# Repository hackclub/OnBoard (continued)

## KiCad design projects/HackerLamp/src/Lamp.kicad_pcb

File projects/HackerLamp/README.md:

---
name: "Aarav Jhamb"
slack_handle: "@AaravJ"
github_handle: "@The-UnknownHacker"
tutorial: None
wokwi: # Link to the Wokwi project if you're submitting for Hacky Holidays
---

# Wifi Powered Lamp

<!-- Describe your board in 2-3 sentences. What are you making? What will it do? -->

It is a wifi powered lamp powered by an ESP32 C3 Xiao and Uses 100 neopixels as power
<!-- How much is it going to cost? -->

Around $29 after including coupons
<!-- Tell us a little bit about your design process. What were some challenging things

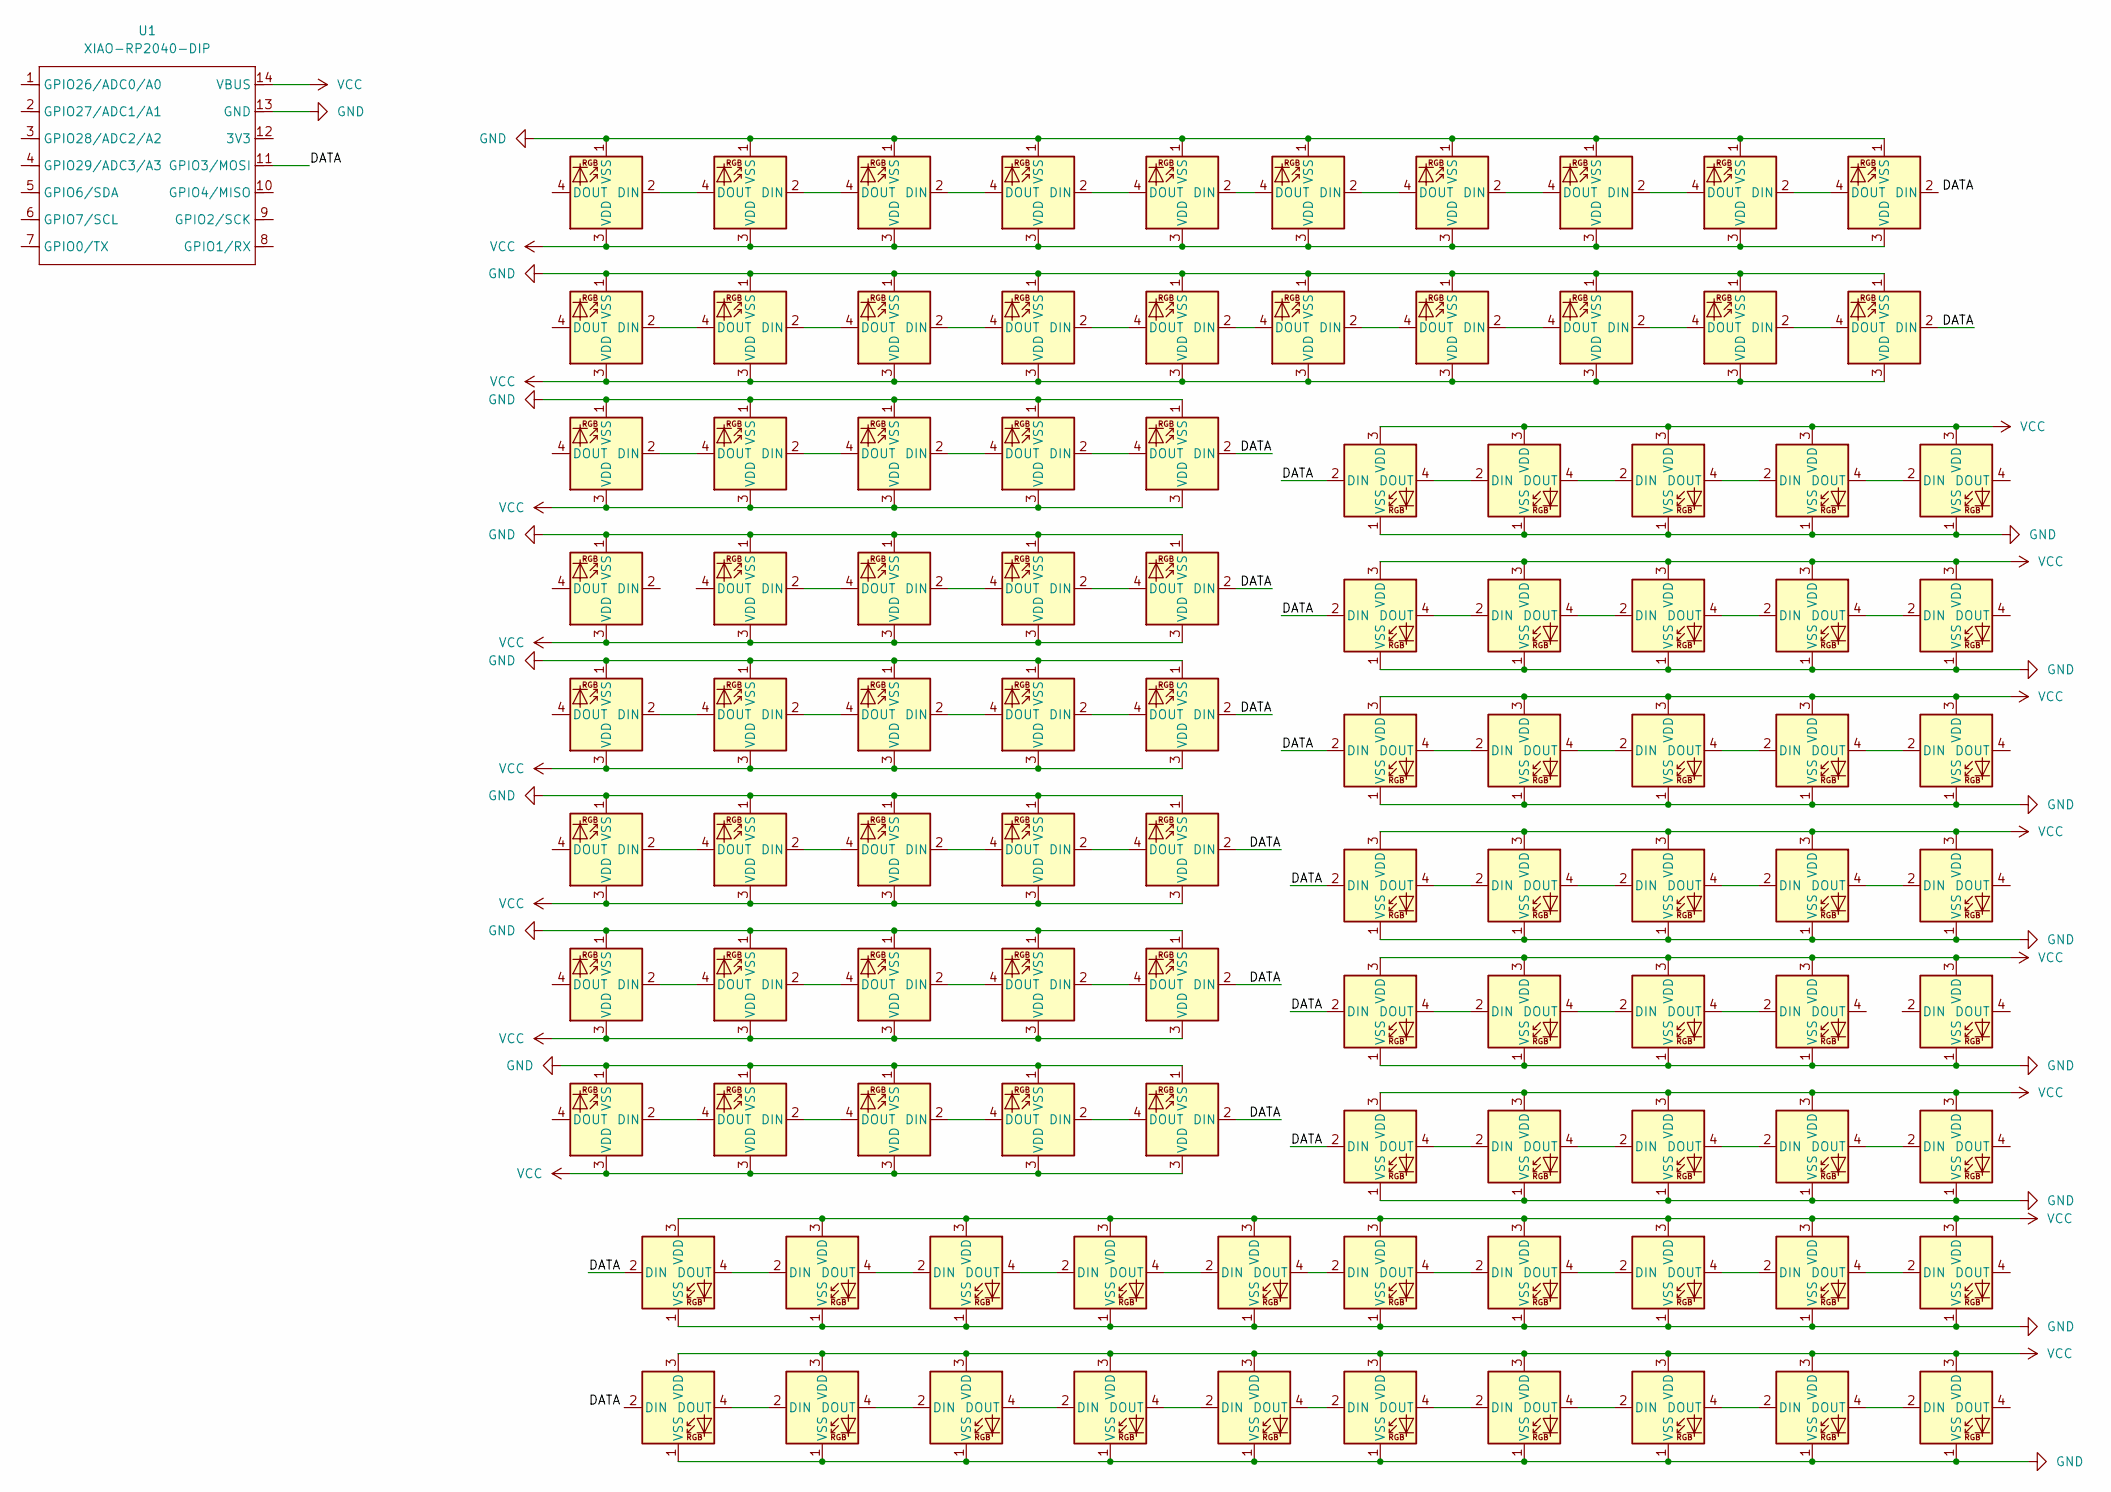
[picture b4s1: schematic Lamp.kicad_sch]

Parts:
D1, D2, D3, D4, D5, D6, D7, D8, D9, D10, D11, D12, D13, D14, D15, D16, D17, D18, D19, D20, D21, D22, D23, D24, D25, D26, D27, D28, D29, D30, D31, D32, D33, D34, D35, D36, D37, D38, D39, D40, D41, D42, D43, D44, D45, D46, D47, D48, D49, D50, D51, D52, D53, D54, D55, D56, D57, D58, D59, D60, D61, D62, D63, D64, D65, D66, D67, D68, D69, D70, D71, D72, D73, D74, D75, D76, D77, D78, D79, D80, D81, D82, D83, D84, D85, D86, D87, D88, D89, D90, D91, D92, D93, D94, D95, D96, D97, D98, D99, D100: SK6812; LED_SK6812_PLCC4_5.0x5.0mm_P3.2mm
U1: XIAO-RP2040-DIP; XIAO-RP2040-SMD

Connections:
/DATA: D1.2 (DIN), D6.2 (DIN), D11.2 (DIN), D12.2 (DIN), D21.2 (DIN), D22.2 (DIN), D41.2 (DIN), D51.2 (DIN), D61.2 (DIN), D62.2 (DIN), D63.2 (DIN), D64.2 (DIN), D65.2 (DIN), D66.2 (DIN), U1.11 (GPIO3/MOSI)
GND: D1.1 (VSS), D2.1 (VSS), D3.1 (VSS), D4.1 (VSS), D5.1 (VSS), D6.1 (VSS), D7.1 (VSS), D8.1 (VSS), D9.1 (VSS), D10.1 (VSS), D11.1 (VSS), D12.1 (VSS), D13.1 (VSS), D14.1 (VSS), D15.1 (VSS), D16.1 (VSS), D17.1 (VSS), D18.1 (VSS), D19.1 (VSS), D20.1 (VSS), D21.1 (VSS), D22.1 (VSS), D23.1 (VSS), D24.1 (VSS), D25.1 (VSS), D26.1 (VSS), D27.1 (VSS), D28.1 (VSS), D29.1 (VSS), D30.1 (VSS), D31.1 (VSS), D32.1 (VSS), D33.1 (VSS), D34.1 (VSS), D35.1 (VSS), D36.1 (VSS), D37.1 (VSS), D38.1 (VSS), D39.1 (VSS), D40.1 (VSS), D41.1 (VSS), D42.1 (VSS), D43.1 (VSS), D44.1 (VSS), D45.1 (VSS), D46.1 (VSS), D47.1 (VSS), D48.1 (VSS), D49.1 (VSS), D50.1 (VSS), D51.1 (VSS), D52.1 (VSS), D53.1 (VSS), D54.1 (VSS), D55.1 (VSS), D56.1 (VSS), D57.1 (VSS), D58.1 (VSS), D59.1 (VSS), D60.1 (VSS), D61.1 (VSS), D62.1 (VSS), D63.1 (VSS), D64.1 (VSS), D65.1 (VSS), D66.1 (VSS), D67.1 (VSS), D68.1 (VSS), D69.1 (VSS), D70.1 (VSS), D71.1 (VSS), D72.1 (VSS), D73.1 (VSS), D74.1 (VSS), D75.1 (VSS), D76.1 (VSS), D77.1 (VSS), D78.1 (VSS), D79.1 (VSS), D80.1 (VSS), D81.1 (VSS), D82.1 (VSS), D83.1 (VSS), D84.1 (VSS), D85.1 (VSS), D86.1 (VSS), D87.1 (VSS), D88.1 (VSS), D89.1 (VSS), D90.1 (VSS), D91.1 (VSS), D92.1 (VSS), D93.1 (VSS), D94.1 (VSS), D95.1 (VSS), D96.1 (VSS), D97.1 (VSS), D98.1 (VSS), D99.1 (VSS), D100.1 (VSS), U1.13 (GND)
unnamed: D1.4 (DOUT), D2.2 (DIN)
unnamed: D2.4 (DOUT), D3.2 (DIN)
unnamed: D3.4 (DOUT), D4.2 (DIN)
unnamed: D4.4 (DOUT), D5.2 (DIN)
unnamed: D6.4 (DOUT), D7.2 (DIN)
unnamed: D7.4 (DOUT), D8.2 (DIN)
unnamed: D8.4 (DOUT), D9.2 (DIN)
unnamed: D9.4 (DOUT), D10.2 (DIN)
unnamed: D11.4 (DOUT), D13.2 (DIN)
unnamed: D12.4 (DOUT), D14.2 (DIN)
unnamed: D13.4 (DOUT), D15.2 (DIN)
unnamed: D14.4 (DOUT), D16.2 (DIN)
unnamed: D15.4 (DOUT), D17.2 (DIN)
unnamed: D16.4 (DOUT), D18.2 (DIN)
unnamed: D17.4 (DOUT), D19.2 (DIN)
unnamed: D18.4 (DOUT), D20.2 (DIN)
unnamed: D21.4 (DOUT), D23.2 (DIN)
unnamed: D22.4 (DOUT), D24.2 (DIN)
unnamed: D23.4 (DOUT), D25.2 (DIN)
unnamed: D24.4 (DOUT), D26.2 (DIN)
unnamed: D25.4 (DOUT), D27.2 (DIN)
unnamed: D26.4 (DOUT), D28.2 (DIN)
unnamed: D28.4 (DOUT), D30.2 (DIN)
unnamed: D31.2 (DIN), D49.4 (DOUT)
unnamed: D31.4 (DOUT), D33.2 (DIN)
unnamed: D32.2 (DIN), D50.4 (DOUT)
unnamed: D32.4 (DOUT), D34.2 (DIN)
unnamed: D33.4 (DOUT), D35.2 (DIN)
unnamed: D34.4 (DOUT), D36.2 (DIN)
unnamed: D35.4 (DOUT), D37.2 (DIN)
unnamed: D36.4 (DOUT), D38.2 (DIN)
unnamed: D37.4 (DOUT), D39.2 (DIN)
unnamed: D38.4 (DOUT), D40.2 (DIN)
unnamed: D41.4 (DOUT), D43.2 (DIN)
unnamed: D42.4 (DOUT), D44.2 (DIN)
unnamed: D43.4 (DOUT), D45.2 (DIN)
unnamed: D44.4 (DOUT), D46.2 (DIN)
unnamed: D45.4 (DOUT), D47.2 (DIN)
unnamed: D46.4 (DOUT), D48.2 (DIN)
unnamed: D47.4 (DOUT), D49.2 (DIN)
unnamed: D48.4 (DOUT), D50.2 (DIN)
unnamed: D51.4 (DOUT), D53.2 (DIN)
unnamed: D52.4 (DOUT), D54.2 (DIN)
unnamed: D53.4 (DOUT), D55.2 (DIN)
unnamed: D54.4 (DOUT), D56.2 (DIN)
unnamed: D55.4 (DOUT), D57.2 (DIN)
unnamed: D56.4 (DOUT), D58.2 (DIN)
unnamed: D57.4 (DOUT), D59.2 (DIN)
unnamed: D58.4 (DOUT), D60.2 (DIN)
unnamed: D59.4 (DOUT), D67.2 (DIN)
unnamed: D60.4 (DOUT), D68.2 (DIN)
unnamed: D61.4 (DOUT), D69.2 (DIN)
unnamed: D62.4 (DOUT), D70.2 (DIN)
unnamed: D63.4 (DOUT), D71.2 (DIN)
unnamed: D64.4 (DOUT), D72.2 (DIN)
unnamed: D65.4 (DOUT), D73.2 (DIN)
unnamed: D66.4 (DOUT), D74.2 (DIN)
unnamed: D67.4 (DOUT), D75.2 (DIN)
unnamed: D68.4 (DOUT), D76.2 (DIN)
unnamed: D69.4 (DOUT), D77.2 (DIN)
unnamed: D70.4 (DOUT), D78.2 (DIN)
unnamed: D71.4 (DOUT), D79.2 (DIN)
unnamed: D72.4 (DOUT), D80.2 (DIN)
unnamed: D73.4 (DOUT), D81.2 (DIN)
unnamed: D74.4 (DOUT), D82.2 (DIN)
unnamed: D75.4 (DOUT), D83.2 (DIN)
unnamed: D76.4 (DOUT), D84.2 (DIN)
unnamed: D77.4 (DOUT), D85.2 (DIN)
unnamed: D78.4 (DOUT), D86.2 (DIN)
unnamed: D79.4 (DOUT), D87.2 (DIN)
unnamed: D80.4 (DOUT), D88.2 (DIN)
unnamed: D81.4 (DOUT), D89.2 (DIN)
unnamed: D82.4 (DOUT), D90.2 (DIN)
unnamed: D83.4 (DOUT), D91.2 (DIN)
unnamed: D84.4 (DOUT), D92.2 (DIN)
unnamed: D85.4 (DOUT), D93.2 (DIN)
unnamed: D86.4 (DOUT), D94.2 (DIN)
unnamed: D87.4 (DOUT), D95.2 (DIN)
unnamed: D88.4 (DOUT), D96.2 (DIN)
unnamed: D90.4 (DOUT), D98.2 (DIN)
unnamed: D91.4 (DOUT), D99.2 (DIN)
unnamed: D92.4 (DOUT), D100.2 (DIN)
VCC: D1.3 (VDD), D2.3 (VDD), D3.3 (VDD), D4.3 (VDD), D5.3 (VDD), D6.3 (VDD), D7.3 (VDD), D8.3 (VDD), D9.3 (VDD), D10.3 (VDD), D11.3 (VDD), D12.3 (VDD), D13.3 (VDD), D14.3 (VDD), D15.3 (VDD), D16.3 (VDD), D17.3 (VDD), D18.3 (VDD), D19.3 (VDD), D20.3 (VDD), D21.3 (VDD), D22.3 (VDD), D23.3 (VDD), D24.3 (VDD), D25.3 (VDD), D26.3 (VDD), D27.3 (VDD), D28.3 (VDD), D29.3 (VDD), D30.3 (VDD), D31.3 (VDD), D32.3 (VDD), D33.3 (VDD), D34.3 (VDD), D35.3 (VDD), D36.3 (VDD), D37.3 (VDD), D38.3 (VDD), D39.3 (VDD), D40.3 (VDD), D41.3 (VDD), D42.3 (VDD), D43.3 (VDD), D44.3 (VDD), D45.3 (VDD), D46.3 (VDD), D47.3 (VDD), D48.3 (VDD), D49.3 (VDD), D50.3 (VDD), D51.3 (VDD), D52.3 (VDD), D53.3 (VDD), D54.3 (VDD), D55.3 (VDD), D56.3 (VDD), D57.3 (VDD), D58.3 (VDD), D59.3 (VDD), D60.3 (VDD), D61.3 (VDD), D62.3 (VDD), D63.3 (VDD), D64.3 (VDD), D65.3 (VDD), D66.3 (VDD), D67.3 (VDD), D68.3 (VDD), D69.3 (VDD), D70.3 (VDD), D71.3 (VDD), D72.3 (VDD), D73.3 (VDD), D74.3 (VDD), D75.3 (VDD), D76.3 (VDD), D77.3 (VDD), D78.3 (VDD), D79.3 (VDD), D80.3 (VDD), D81.3 (VDD), D82.3 (VDD), D83.3 (VDD), D84.3 (VDD), D85.3 (VDD), D86.3 (VDD), D87.3 (VDD), D88.3 (VDD), D89.3 (VDD), D90.3 (VDD), D91.3 (VDD), D92.3 (VDD), D93.3 (VDD), D94.3 (VDD), D95.3 (VDD), D96.3 (VDD), D97.3 (VDD), D98.3 (VDD), D99.3 (VDD), D100.3 (VDD), U1.14 (VBUS)

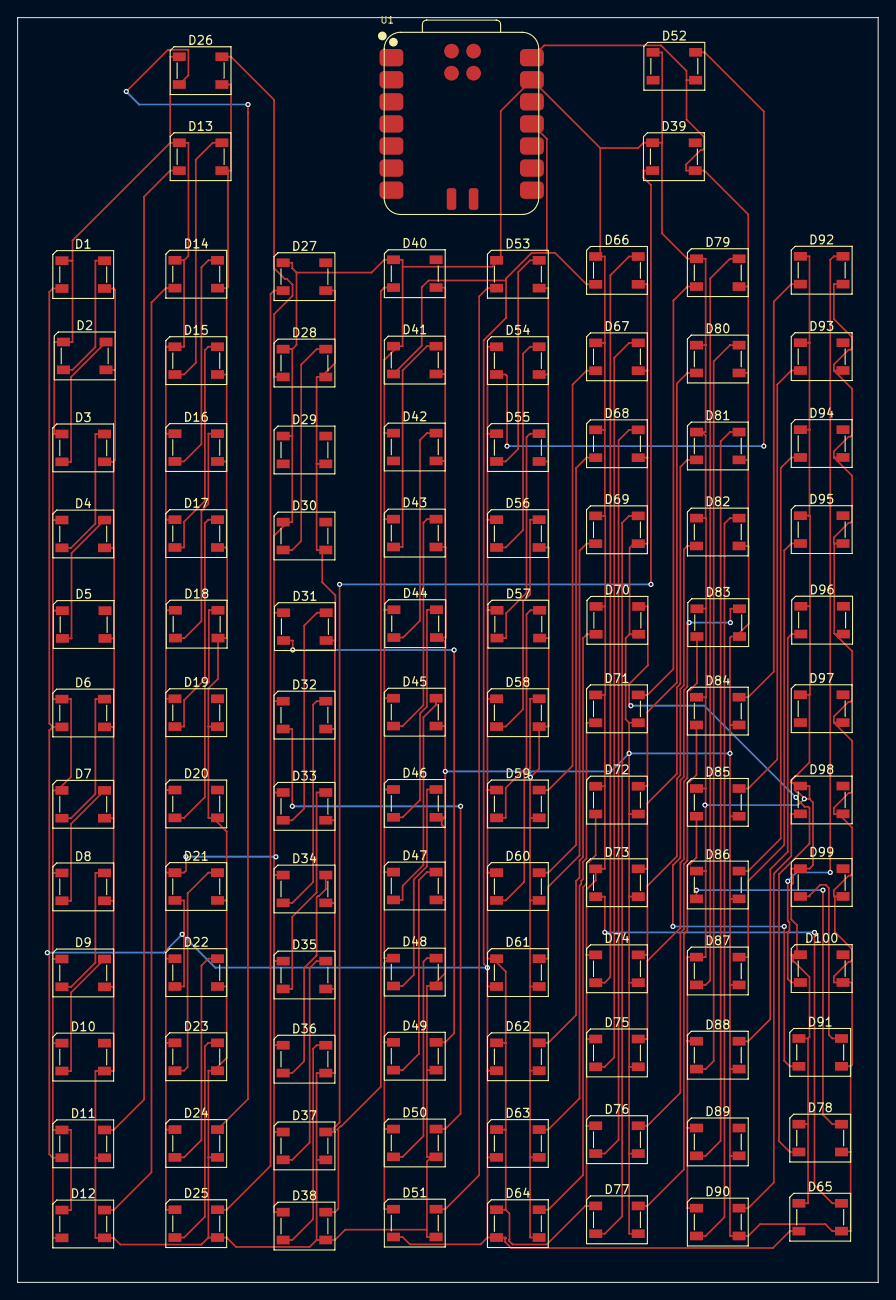
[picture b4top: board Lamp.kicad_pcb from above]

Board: 2 copper layers, 99.0 x 145.5 mm, 101 parts (0 on the bottom side), 85 nets.

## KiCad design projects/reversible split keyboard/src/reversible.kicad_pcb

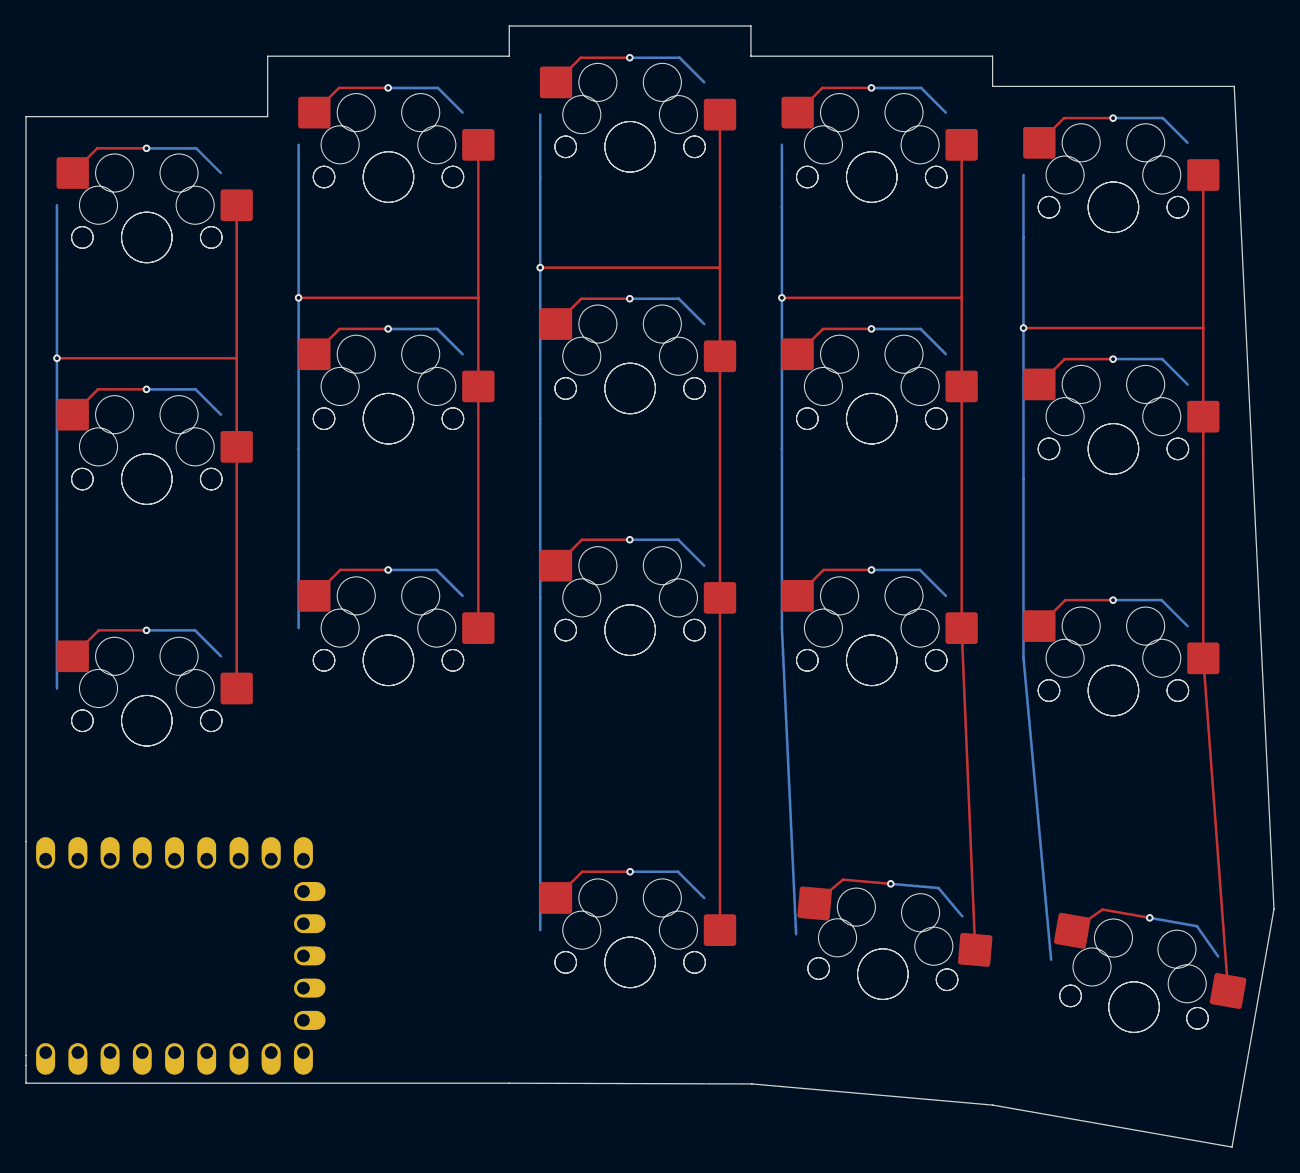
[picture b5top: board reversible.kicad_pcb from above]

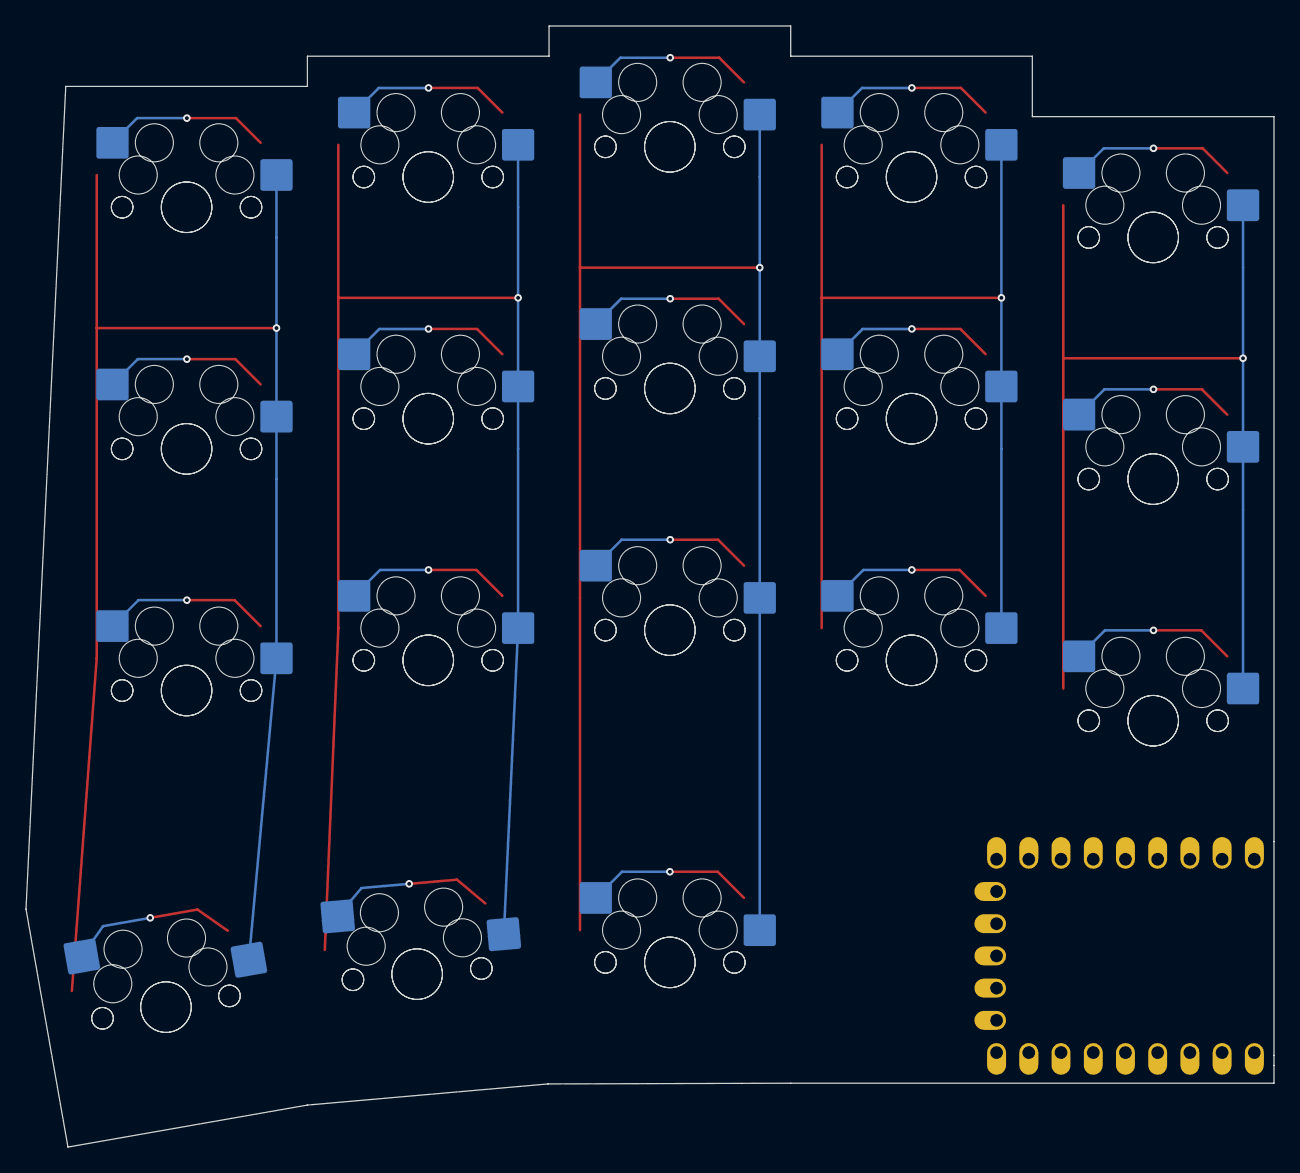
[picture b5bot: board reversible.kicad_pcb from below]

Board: 2 copper layers, 98.4 x 88.4 mm, 37 parts (18 on the bottom side), 23 nets.

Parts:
S1, S1-2, S2, S2-2, S3, S3-2, S4, S4-2, S5, S5-2, S6, S6-2, S7, S7-2, S8, S8-2, S9, S9-2, S10, S10-2, S11, S11-2, S12, S12-2, S13, S13-2, S14, S14-2, S15, S15-2, S16, S16-2, S17, S17-2, S18, S18-2: Keyswitch; MX-Hotswap-1U
U1: RP2040_Zero

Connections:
unnamed: S1.2, S1-2.2
unnamed: S2.2, S2-2.2
unnamed: S3.2, S3-2.2
unnamed: S4.2, S4-2.2
unnamed: S5.2, S5-2.2
unnamed: S6.2, S6-2.2
unnamed: S7.2, S7-2.2
unnamed: S8.2, S8-2.2
unnamed: S9.2, S9-2.2
unnamed: S10.2, S10-2.2
unnamed: S11.2, S11-2.2
unnamed: S12.2, S12-2.2
unnamed: S13.2, S13-2.2
unnamed: S14.2, S14-2.2
unnamed: S15.2, S15-2.2
unnamed: S16.2, S16-2.2
unnamed: S17.2, S17-2.2
unnamed: S18.2, S18-2.2
unnamed: S1.1, S1-2.1, S6.1, S6-2.1, S11.1, S11-2.1
unnamed: S5.1, S5-2.1, S10.1, S10-2.1, S15.1, S15-2.1, S18.1, S18-2.1
unnamed: S2.1, S2-2.1, S7.1, S7-2.1, S12.1, S12-2.1
unnamed: S3.1, S3-2.1, S8.1, S8-2.1, S13.1, S13-2.1, S16.1, S16-2.1
unnamed: S4.1, S4-2.1, S9.1, S9-2.1, S14.1, S14-2.1, S17.1, S17-2.1

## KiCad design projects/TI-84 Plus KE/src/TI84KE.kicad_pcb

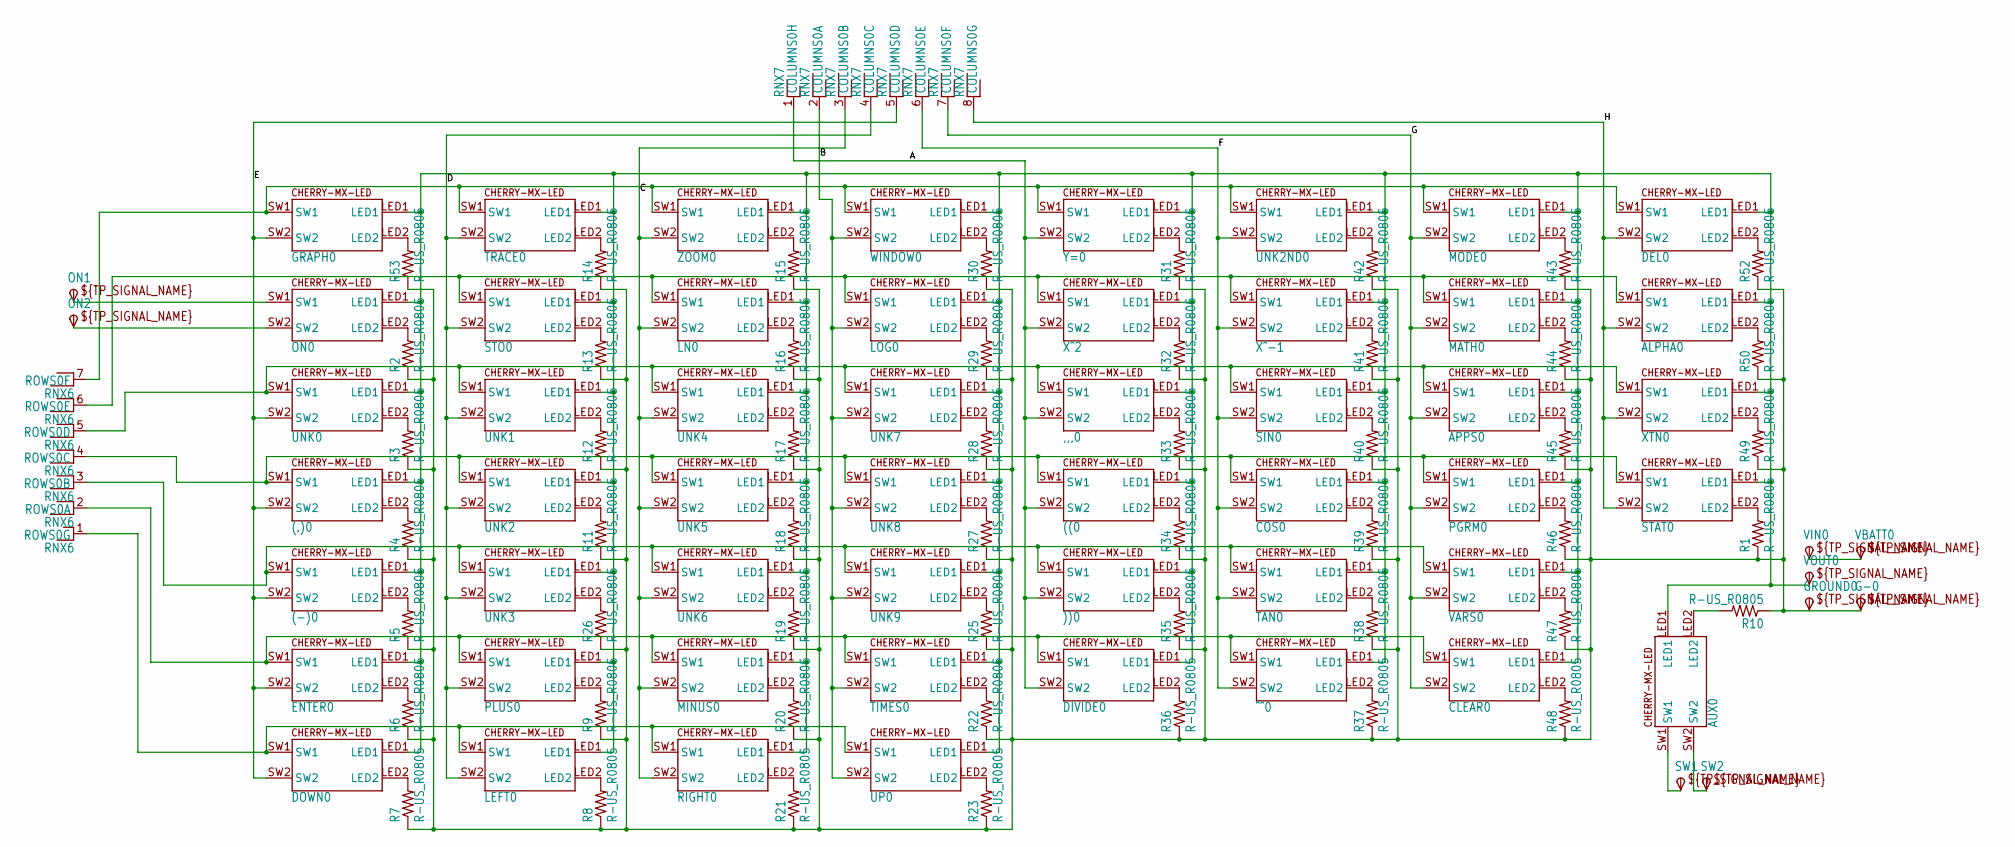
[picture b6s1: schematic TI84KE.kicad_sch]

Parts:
((0: CHERRY-MX-LEDNOSILK; CHERRY-MX-LED-NOSILK
(-)0: CHERRY-MX-LEDNOSILK; CHERRY-MX-LED-NOSILK
(.)0: CHERRY-MX-LEDNOSILK; CHERRY-MX-LED-NOSILK
))0: CHERRY-MX-LEDNOSILK; CHERRY-MX-LED-NOSILK
,,,0: CHERRY-MX-LEDNOSILK; CHERRY-MX-LED-NOSILK
ALPHA0: CHERRY-MX-LEDNOSILK; CHERRY-MX-LED-NOSILK
APPS0: CHERRY-MX-LEDNOSILK; CHERRY-MX-LED-NOSILK
AUX0: CHERRY-MX-LEDNOSILK; CHERRY-MX-LED-NOSILK
CLEAR0: CHERRY-MX-LEDNOSILK; CHERRY-MX-LED-NOSILK
COLUMNS0: RNX7; RN-8
COS0: CHERRY-MX-LEDNOSILK; CHERRY-MX-LED-NOSILK
DEL0: CHERRY-MX-LEDNOSILK; CHERRY-MX-LED-NOSILK
DIVIDE0: CHERRY-MX-LEDNOSILK; CHERRY-MX-LED-NOSILK
DOWN0: CHERRY-MX-LEDNOSILK; CHERRY-MX-LED-NOSILK
ENTER0: CHERRY-MX-LEDNOSILK; CHERRY-MX-LED-NOSILK
G-0: TPSPAD1-17; P1-17
GRAPH0: CHERRY-MX-LEDNOSILK; CHERRY-MX-LED-NOSILK
GROUND0: TPSPAD1-17; P1-17
LEFT0: CHERRY-MX-LEDNOSILK; CHERRY-MX-LED-NOSILK
LN0: CHERRY-MX-LEDNOSILK; CHERRY-MX-LED-NOSILK
LOG0: CHERRY-MX-LEDNOSILK; CHERRY-MX-LED-NOSILK
MATH0: CHERRY-MX-LEDNOSILK; CHERRY-MX-LED-NOSILK
MINUS0: CHERRY-MX-LEDNOSILK; CHERRY-MX-LED-NOSILK
MODE0: CHERRY-MX-LEDNOSILK; CHERRY-MX-LED-NOSILK
ON0: CHERRY-MX-LEDNOSILK; CHERRY-MX-LED-NOSILK
ON1, ON2: TPSPAD1-17; P1-17
PGRM0: CHERRY-MX-LEDNOSILK; CHERRY-MX-LED-NOSILK
PLUS0: CHERRY-MX-LEDNOSILK; CHERRY-MX-LED-NOSILK
R1, R2, R3, R4, R5, R6, R7, R8, R9, R10, R11, R12, R13, R14, R15, R16, R17, R18, R19, R20, R21, R22, R23, R25, R26, R27, R28, R29, R30, R31, R32, R33, R34, R35, R36, R37, R38, R39, R40, R41, R42, R43, R44, R45, R46, R47, R48, R49, R50, R52, R53: R-US_R0805; R0805
RIGHT0: CHERRY-MX-LEDNOSILK; CHERRY-MX-LED-NOSILK
ROWS0: RNX6; RN-7
SIN0: CHERRY-MX-LEDNOSILK; CHERRY-MX-LED-NOSILK
STAT0: CHERRY-MX-LEDNOSILK; CHERRY-MX-LED-NOSILK
STO0: CHERRY-MX-LEDNOSILK; CHERRY-MX-LED-NOSILK
SW1, SW2: TPSPAD1-17; P1-17
TAN0: CHERRY-MX-LEDNOSILK; CHERRY-MX-LED-NOSILK
TIMES0: CHERRY-MX-LEDNOSILK; CHERRY-MX-LED-NOSILK
TRACE0: CHERRY-MX-LEDNOSILK; CHERRY-MX-LED-NOSILK
UNK0, UNK1, UNK2, UNK2ND0, UNK3, UNK4, UNK5, UNK6, UNK7, UNK8, UNK9: CHERRY-MX-LEDNOSILK; CHERRY-MX-LED-NOSILK
UP0: CHERRY-MX-LEDNOSILK; CHERRY-MX-LED-NOSILK
VARS0: CHERRY-MX-LEDNOSILK; CHERRY-MX-LED-NOSILK
VBATT0: TPSPAD1-17; P1-17
VIN0: TPSPAD1-17; P1-17
VOUT0: TPSPAD1-17; P1-17
WINDOW0: CHERRY-MX-LEDNOSILK; CHERRY-MX-LED-NOSILK
XTN0: CHERRY-MX-LEDNOSILK; CHERRY-MX-LED-NOSILK
X^2: CHERRY-MX-LEDNOSILK; CHERRY-MX-LED-NOSILK
X^-1: CHERRY-MX-LEDNOSILK; CHERRY-MX-LED-NOSILK
Y=0: CHERRY-MX-LEDNOSILK; CHERRY-MX-LED-NOSILK
ZOOM0: CHERRY-MX-LEDNOSILK; CHERRY-MX-LED-NOSILK
^^0: CHERRY-MX-LEDNOSILK; CHERRY-MX-LED-NOSILK

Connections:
A: ((0.SW2, ))0.SW2, ,,,0.SW2, COLUMNS0.1, DIVIDE0.SW2, X^2.SW2, Y=0.SW2
B: COLUMNS0.2, LOG0.SW2, TIMES0.SW2, UNK7.SW2, UNK8.SW2, UNK9.SW2, UP0.SW2, WINDOW0.SW2
C: COLUMNS0.3, LN0.SW2, MINUS0.SW2, RIGHT0.SW2, UNK4.SW2, UNK5.SW2, UNK6.SW2, ZOOM0.SW2
D: COLUMNS0.4, LEFT0.SW2, PLUS0.SW2, STO0.SW2, TRACE0.SW2, UNK1.SW2, UNK2.SW2, UNK3.SW2
E: (-)0.SW2, (.)0.SW2, COLUMNS0.5, DOWN0.SW2, ENTER0.SW2, GRAPH0.SW2, UNK0.SW2
F: COLUMNS0.6, COS0.SW2, SIN0.SW2, TAN0.SW2, UNK2ND0.SW2, X^-1.SW2, ^^0.SW2
G: APPS0.SW2, CLEAR0.SW2, COLUMNS0.7, MATH0.SW2, MODE0.SW2, PGRM0.SW2, VARS0.SW2
H: ALPHA0.SW2, COLUMNS0.8, DEL0.SW2, STAT0.SW2, XTN0.SW2
unnamed: DEL0.SW1, GRAPH0.SW1, MODE0.SW1, ROWS0.7, TRACE0.SW1, UNK2ND0.SW1, WINDOW0.SW1, Y=0.SW1, ZOOM0.SW1
unnamed: ALPHA0.SW1, LN0.SW1, LOG0.SW1, MATH0.SW1, ROWS0.6, STO0.SW1, X^2.SW1, X^-1.SW1
unnamed: ,,,0.SW1, APPS0.SW1, ROWS0.5, SIN0.SW1, UNK0.SW1, UNK1.SW1, UNK4.SW1, UNK7.SW1, XTN0.SW1
unnamed: ((0.SW1, (.)0.SW1, COS0.SW1, PGRM0.SW1, ROWS0.4, STAT0.SW1, UNK2.SW1, UNK5.SW1, UNK8.SW1
unnamed: (-)0.SW1, ))0.SW1, ROWS0.3, TAN0.SW1, UNK3.SW1, UNK6.SW1, UNK9.SW1, VARS0.SW1
unnamed: CLEAR0.SW1, DIVIDE0.SW1, ENTER0.SW1, MINUS0.SW1, PLUS0.SW1, ROWS0.2, TIMES0.SW1, ^^0.SW1
unnamed: DOWN0.SW1, LEFT0.SW1, RIGHT0.SW1, ROWS0.1, UP0.SW1
unnamed: ON0.LED2, R2.2
unnamed: R3.2, UNK0.LED2
unnamed: (.)0.LED2, R4.2
unnamed: (-)0.LED2, R5.2
unnamed: ENTER0.LED2, R6.2
unnamed: DOWN0.LED2, R7.2
unnamed: LEFT0.LED2, R8.2
unnamed: PLUS0.LED2, R9.2
unnamed: R11.2, UNK2.LED2
unnamed: R12.2, UNK1.LED2
unnamed: R13.2, STO0.LED2
unnamed: R14.2, TRACE0.LED2
unnamed: R15.2, ZOOM0.LED2
unnamed: LN0.LED2, R16.2
unnamed: R17.2, UNK4.LED2
unnamed: R18.2, UNK5.LED2
unnamed: R19.2, UNK6.LED2
unnamed: MINUS0.LED2, R20.2
unnamed: R21.2, RIGHT0.LED2
unnamed: R22.2, TIMES0.LED2
unnamed: R23.2, UP0.LED2
unnamed: R25.2, UNK9.LED2
unnamed: R26.2, UNK3.LED2
unnamed: R27.2, UNK8.LED2
unnamed: R28.2, UNK7.LED2
unnamed: LOG0.LED2, R29.2
unnamed: R30.2, WINDOW0.LED2
unnamed: R31.2, Y=0.LED2
unnamed: R32.2, X^2.LED2
unnamed: ,,,0.LED2, R33.2
unnamed: ((0.LED2, R34.2
unnamed: ))0.LED2, R35.2
unnamed: DIVIDE0.LED2, R36.2
unnamed: R37.2, ^^0.LED2
unnamed: R38.2, TAN0.LED2
unnamed: COS0.LED2, R39.2
unnamed: R40.2, SIN0.LED2
unnamed: R41.2, X^-1.LED2
unnamed: R42.2, UNK2ND0.LED2
unnamed: MODE0.LED2, R43.2
unnamed: MATH0.LED2, R44.2
unnamed: APPS0.LED2, R45.2
unnamed: PGRM0.LED2, R46.2
unnamed: R47.2, VARS0.LED2
unnamed: CLEAR0.LED2, R48.2
unnamed: GRAPH0.LED2, R53.2
unnamed: R1.2, STAT0.LED2
unnamed: R49.2, XTN0.LED2
unnamed: ALPHA0.LED2, R50.2
unnamed: DEL0.LED2, R52.2
unnamed: AUX0.LED2, R10.2
unnamed: AUX0.SW1, SW1.TP
unnamed: AUX0.SW2, SW2.TP
unnamed: VBATT0.TP, VIN0.TP
unnamed: ON0.SW1, ON1.TP
unnamed: ON0.SW2, ON2.TP
unnamed: ((0.LED1, (-)0.LED1, (.)0.LED1, ))0.LED1, ,,,0.LED1, ALPHA0.LED1, APPS0.LED1, AUX0.LED1, CLEAR0.LED1, COS0.LED1, DEL0.LED1, DIVIDE0.LED1, DOWN0.LED1, ENTER0.LED1, GRAPH0.LED1, LEFT0.LED1, LN0.LED1, LOG0.LED1, MATH0.LED1, MINUS0.LED1, MODE0.LED1, ON0.LED1, PGRM0.LED1, PLUS0.LED1, RIGHT0.LED1, SIN0.LED1, STAT0.LED1, STO0.LED1, TAN0.LED1, TIMES0.LED1, TRACE0.LED1, UNK0.LED1, UNK1.LED1, UNK2.LED1, UNK2ND0.LED1, UNK3.LED1, UNK4.LED1, UNK5.LED1, UNK6.LED1, UNK7.LED1, UNK8.LED1, UNK9.LED1, UP0.LED1, VARS0.LED1, VOUT0.TP, WINDOW0.LED1, XTN0.LED1, X^2.LED1, X^-1.LED1, Y=0.LED1, ZOOM0.LED1, ^^0.LED1

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
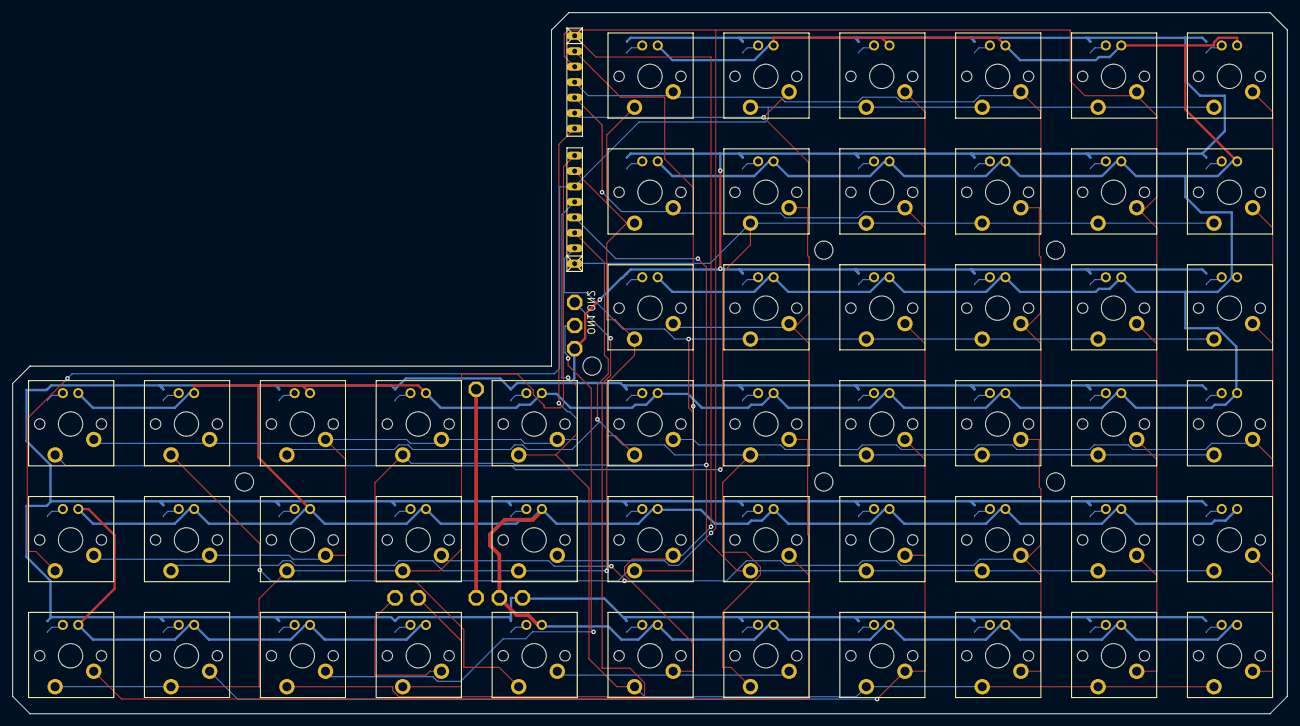
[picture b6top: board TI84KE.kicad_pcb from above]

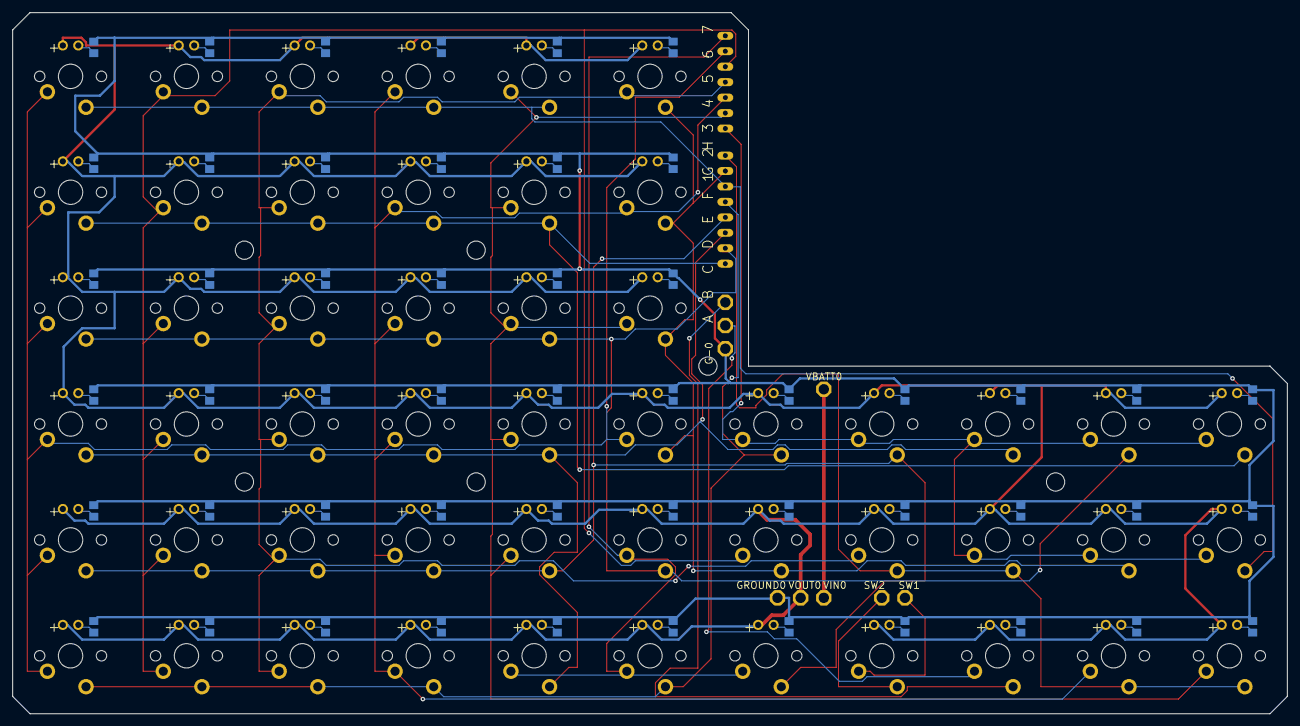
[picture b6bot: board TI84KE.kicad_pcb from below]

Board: 2 copper layers, 209.6 x 115.3 mm, 119 parts (58 on the bottom side), 73 nets.

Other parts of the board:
UNK_HOLE_0: dummyfp0
UNK_HOLE_1: dummyfp1
UNK_HOLE_2: dummyfp2
UNK_HOLE_3: dummyfp3
UNK_HOLE_4: dummyfp4
UNK_HOLE_5: dummyfp5
